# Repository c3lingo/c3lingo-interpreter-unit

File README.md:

# Conference Interpreter Unit
[c3lingo.org](https://c3lingo.org) is doing the great job of translating many talks of the Chaos Communication Congress and other CCC-related events to multiple languages.
But the required hardware for simultaneous translation is quite expensive to rent, even if it's "just" a specialized analog audio mixer.

So the idea was born to design an easy to use hardware with the special requirements of our interpreters in mind.

## Requirements
The hardware unit should deliver the native audio (stage/ hall mix) to the interpreter's headset and provide a sum of all interpreter's microphone to the input of the video streaming/ recording chain.
Mixing of the final translated audio (ducking the native audio with the translation) will be done as part of the streaming/ recording chain, so the interpreter unit should just provide the sum of all microphones.

Normally just 2 interpreters will provide one translation, but demanding talks might require 3 people.
So either 3 headphone inputs/ outputs should be provided or it must be possible to daisy-chain multiple units.

The user interface of the unit should be as simple, as possible to decrease the risk of mis-configuration.
This means, that no compressor and equalizer will be added in the input group.

General requirements:
- Line input of stage/ hall mix (native language) (XLR/ 6.3 mm balanced jack combo connector)
- 3x Microphone input (XLR) (at first just dynamic microphones)
    * VU-Meter for each input channel. (Perhaps with special color scheme: too quiet, good, too loud, clipping)
    * Fader/ Potentiometer for gain control
    * On-Air switch (on/ off position, with state LED)
    * Temporary mute button (momentary switch)
- 3x Headphone output (6.3 mm mono/ stereo (2x mono) jack)
    * Should output mix of native audio, own microphone and other translator's microphone
    * Potentiometer for output volume
    * Potentiometer for volume of own microphone in the mix
    * Potentiometer for volume of other two microphones in the mix
- Outputs:
    * Sum of all translators (XLR/ 6.3 mm balanced jack combo connector)

All inputs (besides the microphones) and outputs should:
- expect/ deliver a nominal level of +6dBu (~1.5 V RMS/ 4.3 V (p-p), german TV broadcast standard, 0 dBu = 0.775 V RMS)
- be transformer balanced and galvanically isolated

This results in a signal flow like this: 

## Status

### Tasks
- [x] Requirements collection
- [x] Electrical design draft/ proof of concept (breadboard)
- [x] Proof of concept validation
- [x] First PCB layout (prototyping modules)
- [x] More testing/ validation
- [x] Second PCB layout + casing prototype
    * [x] Channel strip schematic and PCB design
    * [x] Line I/O schematic and PCB design
    * [x] Power supply
- [x] More testing/ validation

Help is always appreciated!

### Implemented Requirements
- [x] Microphone input
- [x] Line input
- [x] Microphone summing and line output driver
- [x] Adjustable headphone mix and output volume
- [ ] ESD protection of line inputs and outputs
- [x] VU meter (own PCB)
- [x] VU meter (integrated in front panel PCB)
- [x] Mute and On-Air buttons

## Electrical Design
See [electrical-design.md](electrical-design.md).

Components marked as DNP (do not populate) are needed and need to be added.
The mark is just to generate the right BOM for ordering an assembled PBC with all SMD components, but no though-hole parts.

## User Interface
The user interface should enable the interpreters to adjust their microphone gain and headphone mix on their own.
Additionally, a (permanent) on/off switch, as well as a (temporary) mute button should be present.

A possible UI layout might look like this: 

See [hardware-selection.md](hardware-selection.md) for the selection of potentiometers and switches.

### Casing
The casing should be a desk console (angled surface), ideally with space at the front to mount the headset ports (XLR and 6.3 mm jack).
Since it can be quite difficult to drill holes and make the appropriate cutouts on the angled surface, we designed our own housing from bent sheet metal.
See the [mechanical/](mechanical/README.md) directory for additional information.

PCBs are split up by channel and mounting surface, so that dimensional tolerancen between the surfaces are not that critical.
The top plate should have a maximum thickness of 1.5 mm, the front and back can be slightly thicker at 2 mm.
All LEDs need to be mounted with some space to the PCB surface so that they can cover the 9 mm gap to the front plate and still stick through.
A mounting guide can be found at [mechanical/assembly-helpers](mechanical/assembly-helpers/vumeter-leds.scad).

## Notes
A dynamic microphone needs at least 50-60 dB gain in the pre-amp, because a typical signal is at about 1 - 100 uV (-118 to -78 dBu or -120 to -80 dBV).

Line level in professional audio gear is at +4 dBu, which is 1.228 V (RMS).
Because 0 dBu is defined as 1 mW at a load of 600 Ohm, which needs a voltage of 0.77 V.
Increasing the voltage by a factor of 10 is an amplification of 20 dB.

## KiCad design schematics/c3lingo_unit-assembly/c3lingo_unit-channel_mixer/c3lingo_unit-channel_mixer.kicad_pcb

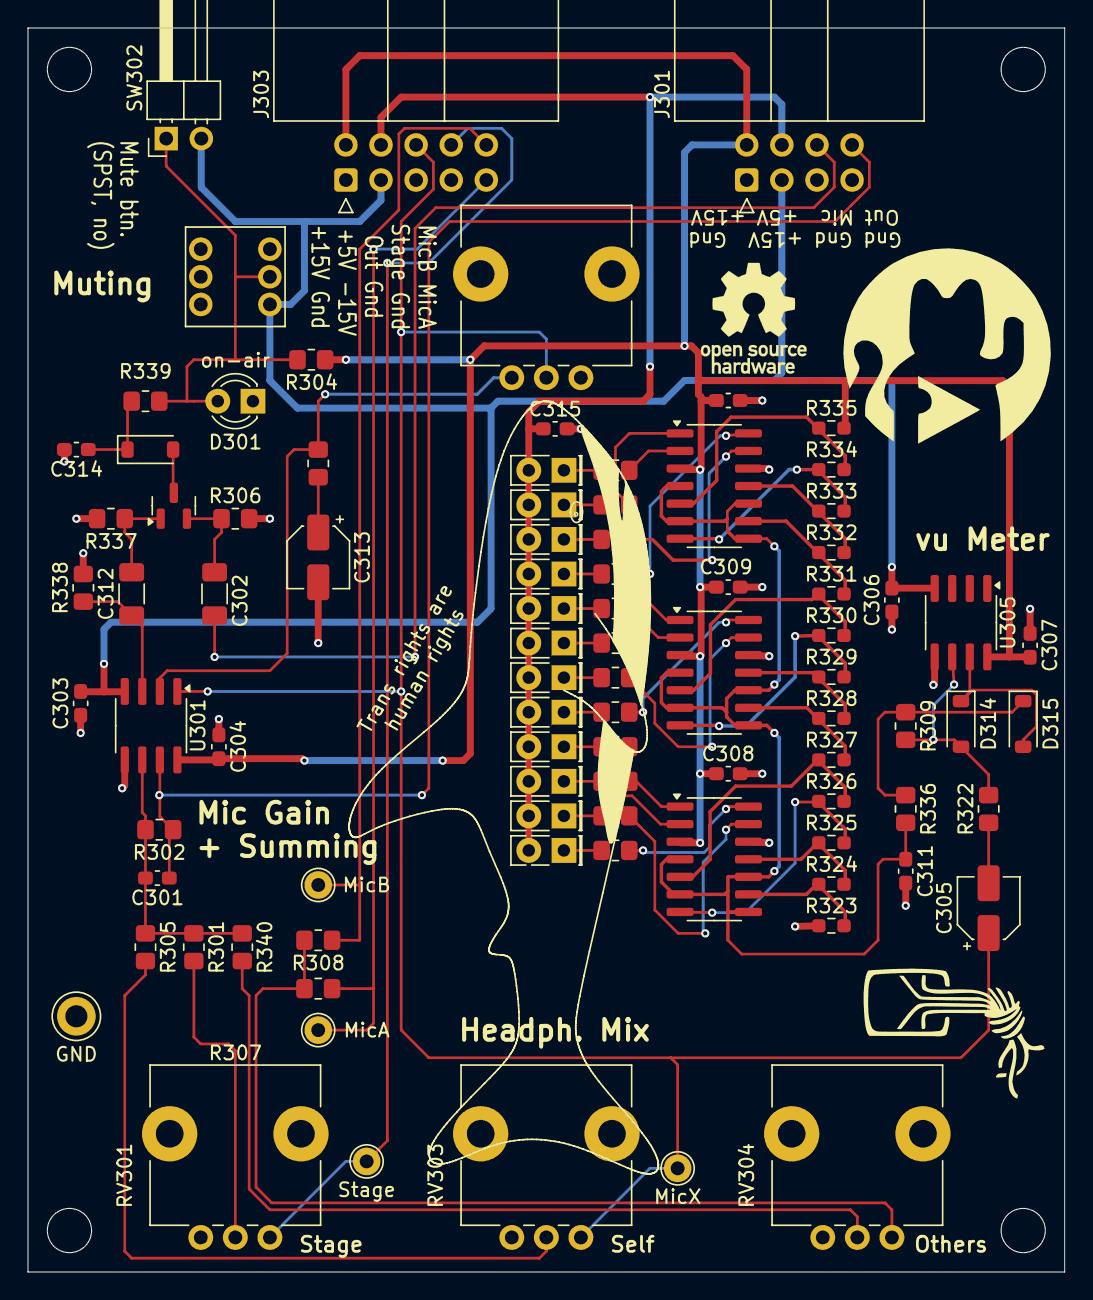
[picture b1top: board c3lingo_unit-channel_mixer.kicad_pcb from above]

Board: 2 copper layers, 75.0 x 90.0 mm, 94 parts (0 on the bottom side), 64 nets.

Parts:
C301: 680pF; C_0603_1608Metric_Pad1.08x0.95mm_HandSolder
C302, C312: 100nF C0G; C_1206_3216Metric_Pad1.33x1.80mm_HandSolder
C303, C304, C306, C307, C308, C309, C310, C311, C314, C315: 100nF; C_0603_1608Metric_Pad1.08x0.95mm_HandSolder
C305, C313: 1uF; CP_Elec_4x5.8
D301: on-air; LED_D3.0mm
D302, D303, D304, D305, D306, D307: ye; LED_Rectangular_W5.0mm_H2.0mm
D308, D309, D310: gn; LED_Rectangular_W5.0mm_H2.0mm
D311, D312, D313: rd; LED_Rectangular_W5.0mm_H2.0mm
D314, D315, D316: 1N4148; D_SOD-123
H301, H302, H303, H304: MountingHole; MountingHole_3.2mm_M3
J301: Interconnect; IDC-Header_2x04_P2.54mm_Horizontal
J303: I/O; IDC-Header_2x05_P2.54mm_Horizontal
Q301: MMBFJ113; SOT-23
R301, R302, R305: 22K; R_0805_2012Metric_Pad1.20x1.40mm_HandSolder
R303: 1.5K; R_0805_2012Metric_Pad1.20x1.40mm_HandSolder
R304: 3.3K; R_0805_2012Metric_Pad1.20x1.40mm_HandSolder
R306, R337, R338, R339: 1M; R_0805_2012Metric_Pad1.20x1.40mm_HandSolder
R307, R308: 2.2K; R_0805_2012Metric_Pad1.20x1.40mm_HandSolder
R309: 12K; R_0805_2012Metric_Pad1.20x1.40mm_HandSolder
R310, R311, R312, R313, R314, R315, R316, R317, R318, R319, R320, R321: 150R; R_0805_2012Metric_Pad1.20x1.40mm_HandSolder
R322: 1K; R_0805_2012Metric_Pad1.20x1.40mm_HandSolder
R323: 220R; R_0603_1608Metric_Pad0.98x0.95mm_HandSolder
R324: 100R; R_0603_1608Metric_Pad0.98x0.95mm_HandSolder
R325: 150R; R_0603_1608Metric_Pad0.98x0.95mm_HandSolder
R326: 180R; R_0603_1608Metric_Pad0.98x0.95mm_HandSolder
R327: 270R; R_0603_1608Metric_Pad0.98x0.95mm_HandSolder
R328: 390R; R_0603_1608Metric_Pad0.98x0.95mm_HandSolder
R329: 470R; R_0603_1608Metric_Pad0.98x0.95mm_HandSolder
R330: 680R; R_0603_1608Metric_Pad0.98x0.95mm_HandSolder
R331: 1.2K; R_0603_1608Metric_Pad0.98x0.95mm_HandSolder
R332: 1.5K; R_0603_1608Metric_Pad0.98x0.95mm_HandSolder
R333: 2.2K; R_0603_1608Metric_Pad0.98x0.95mm_HandSolder
R334: 3.3K; R_0603_1608Metric_Pad0.98x0.95mm_HandSolder
R335: 15K; R_0603_1608Metric_Pad0.98x0.95mm_HandSolder
R336: 100K; R_0805_2012Metric_Pad1.20x1.40mm_HandSolder
R340: 10K; R_0805_2012Metric_Pad1.20x1.40mm_HandSolder
RV301, RV302, RV303, RV304: 50K log.; Potentiometer_CUI_PTN09X_Single_Vertical
SW301: OnAir_X; SW_APEM_MHPS2273_DPDT
SW302: Mute_X; PinHeader_1x02_P2.54mm_Horizontal
TP301: Stage; TestPoint_THTPad_D2.0mm_Drill1.0mm
TP302: MicX; TestPoint_THTPad_D2.0mm_Drill1.0mm
TP303: MicA; TestPoint_THTPad_D2.0mm_Drill1.0mm
TP304: MicB; TestPoint_THTPad_D2.0mm_Drill1.0mm
TP305: GND; TestPoint_Keystone_5005-5009_Compact
U301: TL072; SOIC-8_3.9x4.9mm_P1.27mm
U302, U303, U304: LM339; SOIC-14_3.9x8.7mm_P1.27mm
U305: LM833-N; SOIC-8_3.9x4.9mm_P1.27mm

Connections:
+5V: C315.1, D302.2 (A), D303.2 (A), D304.2 (A), D305.2 (A), D306.2 (A), D307.2 (A), D308.2 (A), D309.2 (A), D310.2 (A), D311.2 (A), D312.2 (A), D313.2 (A), J301.4, J303.4
+15V: C304.2, C307.2, C308.1, C309.1, C310.1, J301.2, J303.2, R304.1, R335.2, U301.8 (V+), U302.3 (V+), U303.3 (V+), U304.3 (V+), U305.8 (V+)
-15V: C303.2, C306.2, J301.3, J303.3, SW301.3 (C), SW302.2, U301.4 (V-), U305.4 (V-)
/Headphone: C301.1, J301.8, R302.1, U301.7
/MicPre: C302.2, J301.6
/Mic_OthersA: J303.9, R307.1, TP303.1
/Mic_OthersB: J303.10, R308.1, TP304.1
/Mic_X: C305.1, J303.6, RV302.2, RV303.3, TP302.1, U301.1
/Stage: J303.8, RV301.3, TP301.1
GND: C303.1, C304.1, C306.1, C307.1, C308.2, C309.2, C310.2, C311.2, C313.2, C314.2, C315.2, D301.1 (K), J301.1, J301.5, J301.7, J303.1, J303.5, J303.7, R306.2, R323.1, R337.2, R338.2, RV301.1, RV303.1, RV304.1, TP305.1, U301.5 (+), U302.12 (V-), U303.12 (V-), U304.12 (V-), U305.5 (+)
unnamed: C305.2, R322.1
unnamed: C313.1, R303.2
unnamed: D301.2 (A), R304.2, R339.2, SW301.2 (B), SW302.1
unnamed: D302.1 (K), R310.1
unnamed: D303.1 (K), R311.1
unnamed: D304.1 (K), R312.1
unnamed: D305.1 (K), R313.1
unnamed: D306.1 (K), R314.1
unnamed: D307.1 (K), R315.1
unnamed: D308.1 (K), R316.1
unnamed: D309.1 (K), R317.1
unnamed: D310.1 (K), R318.1
unnamed: D311.1 (K), R319.1
unnamed: D312.1 (K), R320.1
unnamed: D313.1 (K), R321.1
unnamed: D314.2 (A), R309.2, R322.2, U305.6 (-)
unnamed: D314.1 (K), D315.2 (A), U305.7
unnamed: D315.1 (K), R309.1, R336.1
unnamed: D316.2 (A), Q301.3 (G)
unnamed: C314.1, D316.1 (K), R339.1
unnamed: C312.2, Q301.1 (D), R337.1
unnamed: C302.1, Q301.2 (S), R306.1
unnamed: R301.2, RV301.2
unnamed: R305.2, RV303.2
unnamed: R307.2, R308.2, RV304.3
unnamed: R310.2, U302.14
unnamed: R311.2, U302.13
unnamed: R312.2, U302.1
unnamed: R313.2, U302.2
unnamed: R314.2, U303.14
unnamed: R315.2, U303.13
unnamed: R316.2, U303.1
unnamed: R317.2, U303.2
unnamed: R318.2, U304.14
unnamed: R319.2, U304.13
unnamed: R320.2, U304.1
unnamed: R321.2, U304.2
unnamed: R340.2, RV304.2
unnamed: C312.1, R338.1, U301.3 (+)
unnamed: R303.1, RV302.1, U301.2 (-)
unnamed: C301.2, R301.1, R302.2, R305.1, R340.1, U301.6 (-)
unnamed: R326.2, R327.1, U302.5 (+)
unnamed: C311.1, R336.2, U302.4 (-), U302.6 (-), U302.8 (-), U302.10 (-), U303.4 (-), U303.6 (-), U303.8 (-), U303.10 (-), U304.4 (-), U304.6 (-), U304.8 (-), U304.10 (-)
unnamed: R325.2, R326.1, U302.7 (+)
unnamed: R324.2, R325.1, U302.11 (+)
unnamed: R323.2, R324.1, U302.9 (+)
unnamed: R330.2, R331.1, U303.5 (+)
unnamed: R329.2, R330.1, U303.7 (+)
unnamed: R328.2, R329.1, U303.11 (+)
unnamed: R327.2, R328.1, U303.9 (+)
unnamed: R334.2, R335.1, U304.5 (+)
unnamed: R333.2, R334.1, U304.7 (+)
unnamed: R332.2, R333.1, U304.11 (+)
unnamed: R331.2, R332.1, U304.9 (+)

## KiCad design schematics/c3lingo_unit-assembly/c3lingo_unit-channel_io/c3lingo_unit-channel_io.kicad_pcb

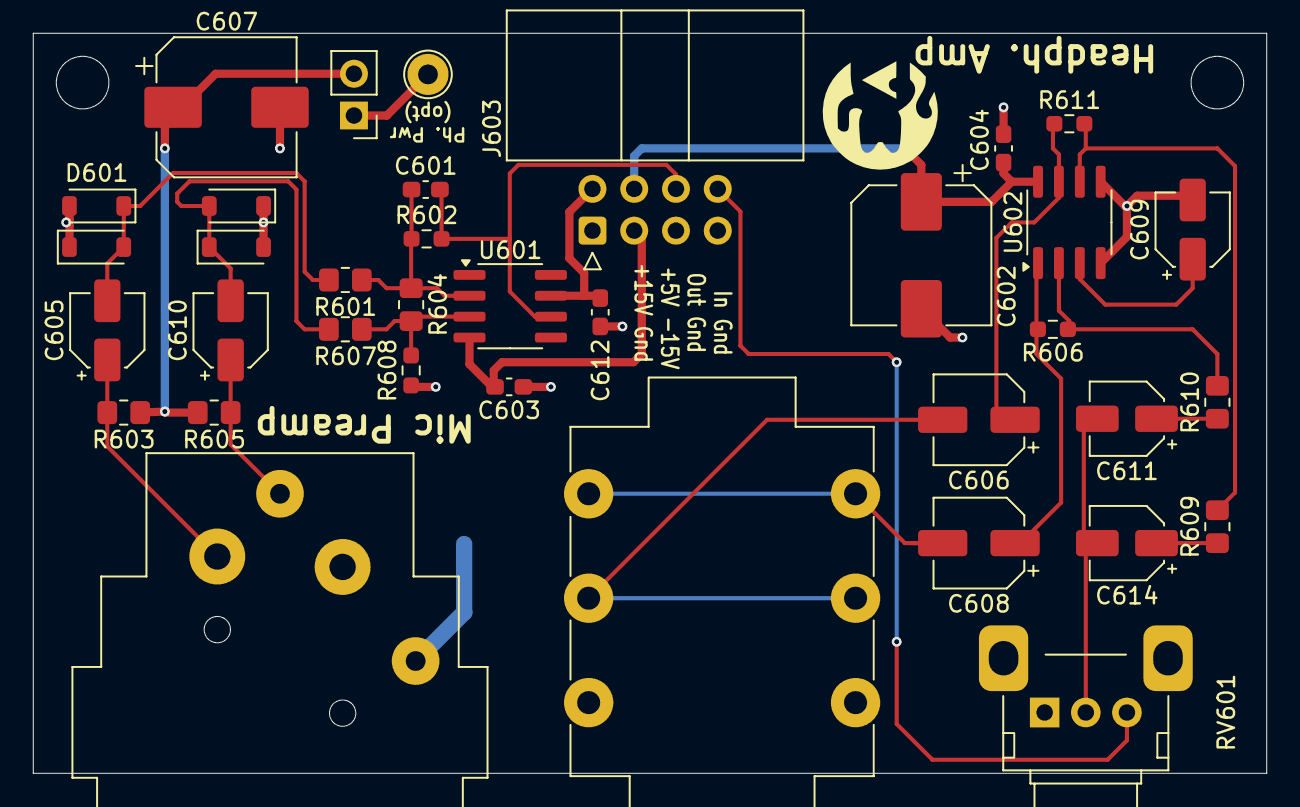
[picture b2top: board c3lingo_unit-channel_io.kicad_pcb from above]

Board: 2 copper layers, 75.0 x 45.0 mm, 39 parts (1 on the bottom side), 25 nets.

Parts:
C601: 330p; C_0603_1608Metric_Pad1.08x0.95mm_HandSolder
C602: 100uF; CP_Elec_8x10
C603, C604, C612: 100nF, lowESR; C_0603_1608Metric_Pad1.08x0.95mm_HandSolder
C605, C610: 1uF/ 63V lowESR; CP_Elec_4x5.8
C606, C608: 68uF lowESR; CP_Elec_5x5.8
C607: 100uF/ 50V; CP_Elec_8x10
C609: 1uF lowESR; CP_Elec_4x5.8
C611, C614: 1uF; CP_Elec_4x5.8
D601, D602, D603, D604: 1N4148; D_SOD-123
H601, H602: MountingHole; MountingHole_3.2mm_M3
J601: Mic X In; Jack_XLR_Neutrik_NC3FAAH2_Horizontal
J602: Headphone X; Jack_6.35mm_Neutrik_NMJ6HFD2_Horizontal
J603: Interconnect; IDC-Header_2x04_P2.54mm_Horizontal
JP601: GND_JMP; SolderJumper-2_P1.3mm_Open_TrianglePad1.0x1.5mm
JP602: Phant. Pwr; PinHeader_1x02_P2.54mm_Vertical
R601, R607: 1K 1%; R_0805_2012Metric_Pad1.20x1.40mm_HandSolder
R602, R608: 39K 1%; R_0603_1608Metric_Pad0.98x0.95mm_HandSolder
R603, R605: 6.8K 1%; R_0805_2012Metric_Pad1.20x1.40mm_HandSolder
R604: 27K 1%; R_0805_2012Metric_Pad1.20x1.40mm_HandSolder
R606, R611: 39K; R_0603_1608Metric_Pad0.98x0.95mm_HandSolder
R609, R610: 10K; R_0805_2012Metric_Pad1.20x1.40mm_HandSolder
RV601: 50K log.; Potentiometer_Alps_RK09K_Single_Horizontal
TP601: Phantom Power; TestPoint_THTPad_D2.5mm_Drill1.2mm
U601: NE5534; SOIC-8_3.9x4.9mm_P1.27mm
U602: TPA6111A2; SOIC-8_3.9x4.9mm_P1.27mm

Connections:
+5V: C602.1, C604.1, J603.4, U602.8 (VDD)
+15V: C612.1, J603.2, U601.7 (V+)
-15V: C603.2, J603.3, U601.4 (V-)
/Headphone: J603.8, RV601.3
/MicPre: C601.2, J603.6, R602.2, U601.6
GND: C602.2, C603.1, C604.2, C607.2, C609.2, C612.2, D601.2 (A), D602.1 (K), D603.1 (K), D604.2 (A), J601.1, J602.S, J602.SN, J603.1, J603.5, J603.7, JP601.1 (A), R608.1, RV601.1, U602.4 (GND), U602.5 (SHDN)
GNDREF: J601.G, JP601.2 (B)
unnamed: C605.1, J601.2, R603.2
unnamed: C606.2, J602.R, J602.RN
unnamed: C608.2, J602.T, J602.TN
unnamed: C610.1, J601.3, R605.1
unnamed: C611.1, R610.1
unnamed: C611.2, C614.2, RV601.2
unnamed: C614.1, R609.1
unnamed: C605.2, D601.1 (K), D602.2 (A), R601.2
unnamed: C610.2, D603.2 (A), D604.1 (K), R607.2
unnamed: JP602.1 (A), TP601.1
unnamed: R604.2, R607.1, R608.2, U601.3 (+)
unnamed: C601.1, R601.1, R602.1, R604.1, U601.2 (-)
unnamed: C609.1, U602.3 (BYPASS)
unnamed: R606.1, R610.2, U602.2 (IN1-)
unnamed: R609.2, R611.2, U602.6 (IN2-)
unnamed: C608.1, R606.2, U602.1 (VO1)
unnamed: C606.1, R611.1, U602.7 (VO2)
V_Phant: C607.1, JP602.2 (B), R603.1, R605.2

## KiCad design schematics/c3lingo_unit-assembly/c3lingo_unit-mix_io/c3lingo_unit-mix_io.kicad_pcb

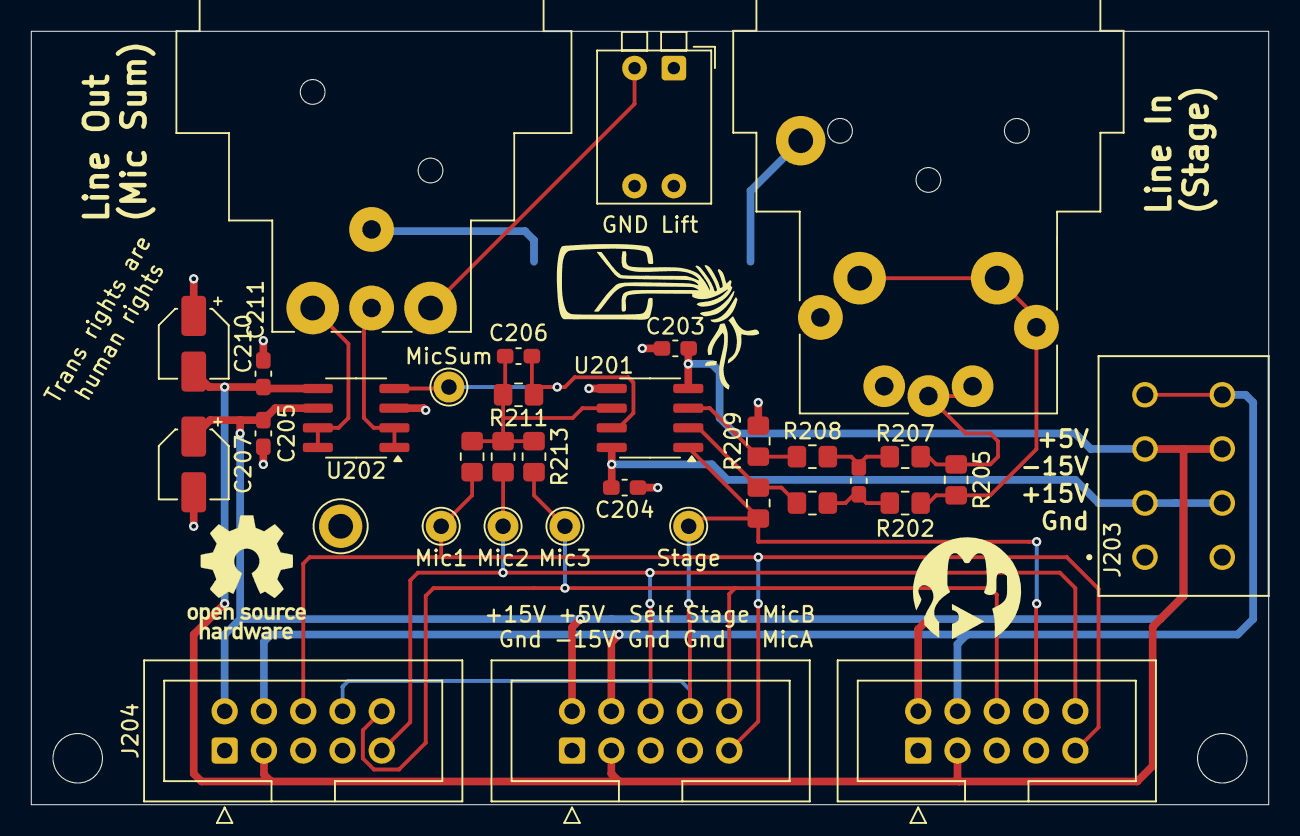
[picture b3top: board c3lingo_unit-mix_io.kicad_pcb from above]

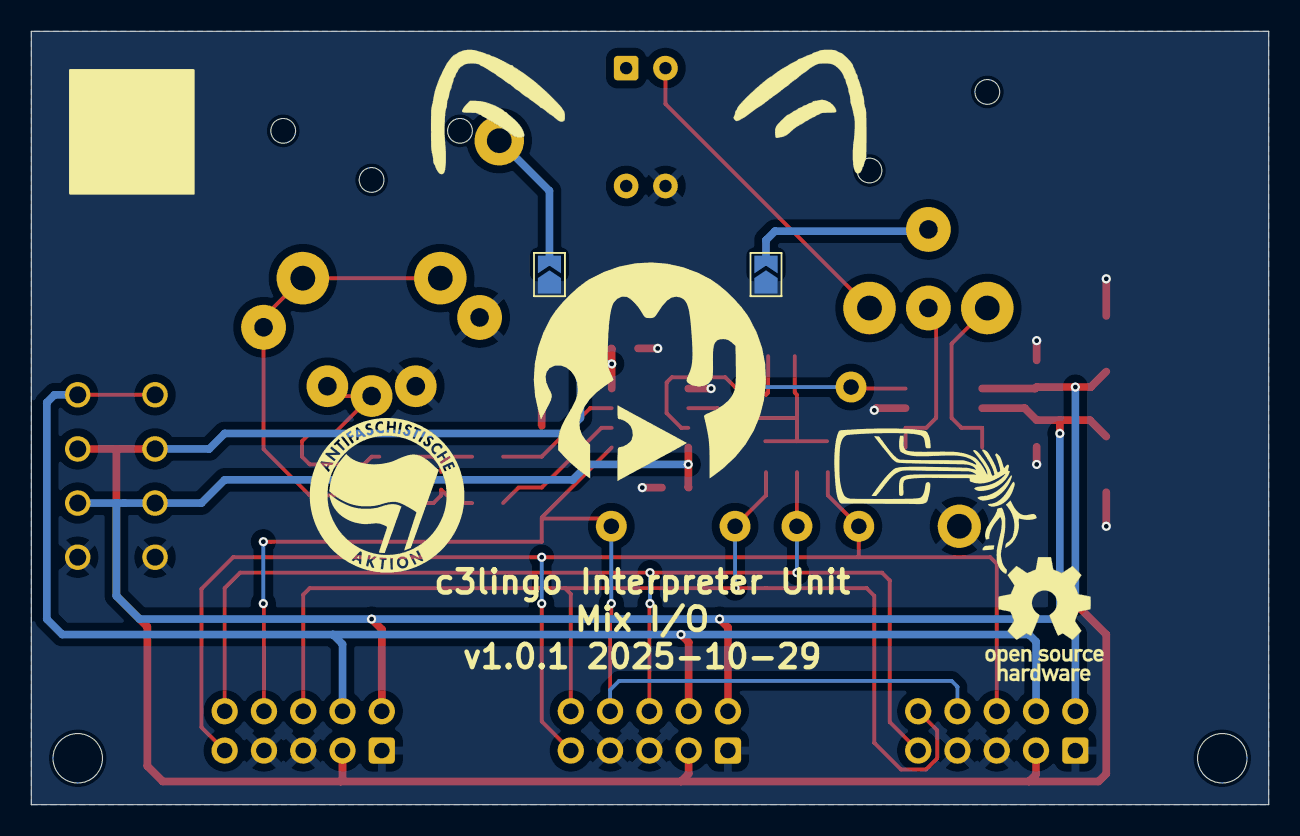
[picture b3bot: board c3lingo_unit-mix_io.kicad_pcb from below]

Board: 2 copper layers, 80.0 x 50.0 mm, 38 parts (2 on the bottom side), 20 nets.

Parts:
C202: 220pF; C_0603_1608Metric_Pad1.08x0.95mm_HandSolder
C203, C204, C205, C211: 100nF; C_0603_1608Metric_Pad1.08x0.95mm_HandSolder
C206: 22pF; C_0603_1608Metric_Pad1.08x0.95mm_HandSolder
C207, C210: 10uF; CP_Elec_4x5.4
H201, H202: MountingHole; MountingHole_3.2mm_M3
J201: Stage Line-In; Jack_XLR-6.35mm_Neutrik_NCJ6FA-H_Horizontal
J202: Mix Line-Out; Jack_XLR_Neutrik_NC3MAAH_Horizontal
J203: PowerSupply; TerminalBlock_Phoenix_SPTAF-1-4-3.5_1x04_P3.5mm
J204: Ch1; IDC-Header_2x05_P2.54mm_Vertical
J205: Ch2; IDC-Header_2x05_P2.54mm_Vertical
J206: Ch3; IDC-Header_2x05_P2.54mm_Vertical
JP201, JP202: GND_JMP; SolderJumper-2_P1.3mm_Open_TrianglePad1.0x1.5mm
R201, R202, R203, R207, R208, R209, R211: 10K; R_0805_2012Metric_Pad1.20x1.40mm_HandSolder
R205: 3.3K; R_0805_2012Metric_Pad1.20x1.40mm_HandSolder
R210, R212, R213: 22K; R_0805_2012Metric_Pad1.20x1.40mm_HandSolder
SW201: GND Lift; SW_DIP_SPSTx02_Piano_CTS_Series194-2MSTN_W7.62mm_P2.54mm
TP201: Stage; TestPoint_THTPad_D2.0mm_Drill1.0mm
TP202: Mic1; TestPoint_THTPad_D2.0mm_Drill1.0mm
TP203: Mic2; TestPoint_THTPad_D2.0mm_Drill1.0mm
TP204: MicSum; TestPoint_THTPad_D2.0mm_Drill1.0mm
TP205: Mic3; TestPoint_THTPad_D2.0mm_Drill1.0mm
TP206: GND; TestPoint_Keystone_5005-5009_Compact
U201: LM833-N; SOIC-8_3.9x4.9mm_P1.27mm
U202: DRV135UA; SOIC-8_3.9x4.9mm_P1.27mm

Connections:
+5V: J203.4, J204.4, J205.4, J206.4
+15V: C204.2, C205.1, C207.1, J203.2, J204.2, J205.2, J206.2, U201.8 (V+), U202.6 (V+)
-15V: C203.2, C210.2, C211.1, J203.3, J204.3, J205.3, J206.3, U201.4 (V-), U202.5 (V-)
/Mic_Ch1: J204.6, J205.9, J206.9, R210.2, TP202.1
/Mic_Ch2: J204.9, J205.6, J206.10, R212.2, TP203.1
/Mic_Ch3: J204.10, J205.10, J206.6, R213.2, TP205.1
/Stage: J204.8, J205.8, J206.8, R201.1, TP201.1, U201.1
GND: C203.1, C204.1, C205.2, C207.2, C210.1, C211.2, J201.1, J201.S, J203.1, J204.1, J204.5, J204.7, J205.1, J205.5, J205.7, J206.1, J206.5, J206.7, JP201.1 (A), JP202.1 (A), R209.2, SW201.3, TP206.1, U201.5 (+), U202.3 (GND)
GNDREF: J201.G, J202.G, JP201.2 (B), JP202.2 (B)
unnamed: C202.1, R202.2, R203.2
unnamed: C202.2, R207.2, R208.2
unnamed: J201.2, J201.T, R202.1, R205.2
unnamed: J201.3, J201.R, R205.1, R207.1
unnamed: J202.1, SW201.2
unnamed: R208.1, R209.1, U201.3 (+)
unnamed: R201.2, R203.1, U201.2 (-)
unnamed: C206.2, R210.1, R211.2, R212.1, R213.1, U201.6 (-)
unnamed: J202.2, U202.7 (SENSE+), U202.8 (VO+)
unnamed: J202.3, U202.1 (VO-), U202.2 (SENSE-)
unnamed: C206.1, R211.1, TP204.1, U201.7, U202.4 (VIN)

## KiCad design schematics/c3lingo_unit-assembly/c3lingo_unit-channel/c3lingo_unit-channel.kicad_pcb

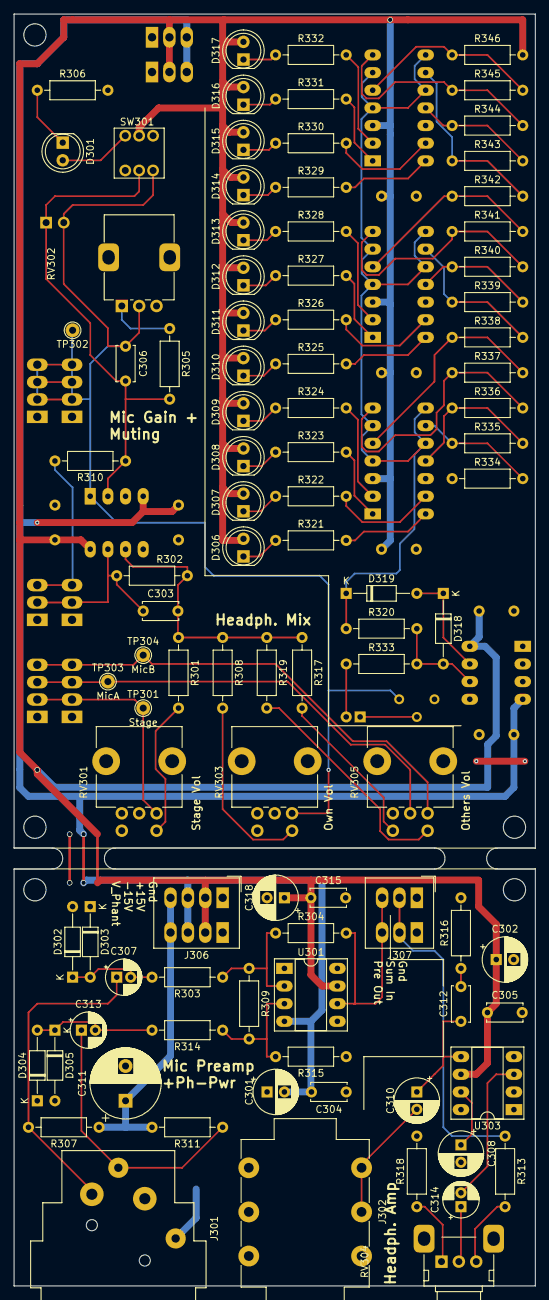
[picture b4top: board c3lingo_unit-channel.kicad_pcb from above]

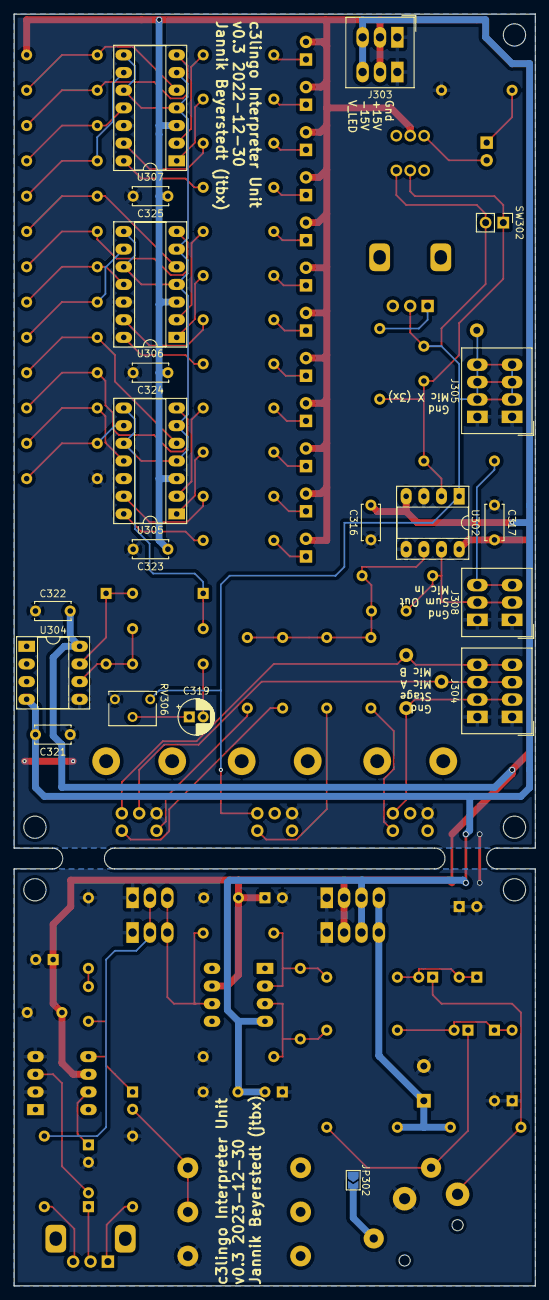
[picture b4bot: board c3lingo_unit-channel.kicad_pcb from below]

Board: 2 copper layers, 75.0 x 183.0 mm, 120 parts (20 on the bottom side), 77 nets.

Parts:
C301, C302, C308, C318: 100uF; CP_Radial_D6.3mm_P2.50mm
C303: 22pF; C_Disc_D5.0mm_W2.5mm_P5.00mm
C304, C305, C306, C315, C316, C317, C321, C322, C323, C324, C325: 100nF; C_Disc_D5.0mm_W2.5mm_P5.00mm
C307, C313: 1uF/ 63V lowESR; CP_Radial_D5.0mm_P2.00mm
C310: 220uF lowESR; CP_Radial_D6.3mm_P2.50mm
C311: 100uF/ 63V; CP_Radial_D10.0mm_P5.00mm
C312: 47nF; C_Disc_D5.0mm_W2.5mm_P5.00mm
C314, C319: 1uF; CP_Radial_D5.0mm_P2.00mm
D301: On-Air (rd); LED_D5.0mm
D302, D303, D304, D305, D318, D319: 1N4148; D_DO-35_SOD27_P10.16mm_Horizontal
D306, D307, D308, D309, D317: rd; LED_D5.0mm
D310, D311, D315, D316: ye; LED_D5.0mm
D312, D313, D314: gn; LED_D5.0mm
H301, H302, H303, H305, H306: MountingHole; MountingHole_3.2mm_M3
J301: Mic X In; Jack_XLR_Neutrik_NC3FAAH2_Horizontal
J302: Headphone X; Jack_6.35mm_Neutrik_NMJ6HFD2_Horizontal
J303: PowerSupply; TerminalBlock_Phoenix_PTSM-0,5-3-2.5-H-THR_1x03_P2.50mm_Hor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
J304: Inputs; TerminalBlock_Phoenix_PTSM-0,5-4-2.5-H-THR_1x04_P2.50mm_Hor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
J305: Output; TerminalBlock_Phoenix_PTSM-0,5-4-2.5-H-THR_1x04_P2.50mm_Hor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
J306: PowerSupply; TerminalBlock_Phoenix_PTSM-0,5-4-2.5-H-THR_1x04_P2.50mm_Hor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
J307, J308: Interconnect; TerminalBlock_Phoenix_PTSM-0,5-3-2.5-H-THR_1x03_P2.50mm_Hor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
JP302: GND_JMP; SolderJumper-2_P1.3mm_Open_TrianglePad1.0x1.5mm
R301, R302, R308, R317, R319: 22K; R_Axial_DIN0207_L6.3mm_D2.5mm_P10.16mm_Horizontal
R303, R314: 1K 1%; R_Axial_DIN0207_L6.3mm_D2.5mm_P10.16mm_Horizontal
R304, R315: 330K 1%; R_Axial_DIN0207_L6.3mm_D2.5mm_P10.16mm_Horizontal
R305: 56R; R_Axial_DIN0207_L6.3mm_D2.5mm_P10.16mm_Horizontal
R306, R341: 680R; R_Axial_DIN0207_L6.3mm_D2.5mm_P10.16mm_Horizontal
R307, R311: 6.8K 1%; R_Axial_DIN0207_L6.3mm_D2.5mm_P10.16mm_Horizontal
R309: 27K 1%; R_Axial_DIN0207_L6.3mm_D2.5mm_P10.16mm_Horizontal
R310: 330R; R_Axial_DIN0207_L6.3mm_D2.5mm_P10.16mm_Horizontal
R313: 330K; R_Axial_DIN0207_L6.3mm_D2.5mm_P10.16mm_Horizontal
R316: 12R; R_Axial_DIN0207_L6.3mm_D2.5mm_P10.16mm_Horizontal
R318: 2.2K; R_Axial_DIN0207_L6.3mm_D2.5mm_P10.16mm_Horizontal
R320: 15K; R_Axial_DIN0207_L6.3mm_D2.5mm_P10.16mm_Horizontal
R321, R322, R323, R324, R325, R326, R327, R328, R329, R330, R331, R332, R340: 390R; R_Axial_DIN0207_L6.3mm_D2.5mm_P10.16mm_Horizontal
R333, R342: 1K; R_Axial_DIN0207_L6.3mm_D2.5mm_P10.16mm_Horizontal
R334, R336: 68R; R_Axial_DIN0207_L6.3mm_D2.5mm_P10.16mm_Horizontal
R335: 39R; R_Axial_DIN0207_L6.3mm_D2.5mm_P10.16mm_Horizontal
R337: 100R; R_Axial_DIN0207_L6.3mm_D2.5mm_P10.16mm_Horizontal
R338: 150R; R_Axial_DIN0207_L6.3mm_D2.5mm_P10.16mm_Horizontal
R339: 270R; R_Axial_DIN0207_L6.3mm_D2.5mm_P10.16mm_Horizontal
R343: 1.5K; R_Axial_DIN0207_L6.3mm_D2.5mm_P10.16mm_Horizontal
R344, R346: 2.7K; R_Axial_DIN0207_L6.3mm_D2.5mm_P10.16mm_Horizontal
R345: 3.9K; R_Axial_DIN0207_L6.3mm_D2.5mm_P10.16mm_Horizontal
RV301, RV303: 50K log.; Potentiometer_Alps_RK09K_Double_Vertical
RV302: 10K log.; Potentiometer_Alps_RK09K_Single_Vertical
RV304: 50K log.; Potentiometer_Alps_RK09K_Single_Horizontal
RV305: 50K log. st.; Potentiometer_Alps_RK09K_Double_Vertical
RV306: 50K; Potentiometer_Vishay_T73XX_Horizontal
SW301: OnAir_X; SW_APEM_MHPS2273_DPDT
SW302: Mute_X; PinHeader_1x02_P2.54mm_Vertical
TP301: Stage; TestPoint_THTPad_D2.0mm_Drill1.0mm
TP302: MicX; TestPoint_THTPad_D2.0mm_Drill1.0mm
TP303: MicA; TestPoint_THTPad_D2.0mm_Drill1.0mm
TP304: MicB; TestPoint_THTPad_D2.0mm_Drill1.0mm
U301: NE5534; DIP-8_W7.62mm_Socket_LongPads
U302, U304: LM833N; DIP-8_W7.62mm_Socket_LongPads
U303: LM386N-4; DIP-8_W7.62mm_Socket_LongPads
U305, U306, U307: LM339; DIP-14_W7.62mm_Socket_LongPads

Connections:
+15V: C302.1, C305.1, C315.1, C317.2, C318.1, C322.2, C323.1, C324.1, C325.1, D306.2 (A), D307.2 (A), D308.2 (A), D309.2 (A), D310.2 (A), D311.2 (A), D312.2 (A), D313.2 (A), D314.2 (A), D315.2 (A), D316.2 (A), D317.2 (A), J303.2, J306.2, R346.2, SW301.5 (B), U301.7 (V+), U302.8 (V+), U303.6 (V+), U304.8 (V+), U305.3 (V+), U306.3 (V+), U307.3 (V+)
-15V: C301.2, C304.2, C316.2, C321.2, J303.3, J306.3, U301.4 (V-), U302.4 (V-), U304.4 (V-)
/Monitor_OthersA: J304.3, RV305.6, TP303.1
/Monitor_OthersB: J304.4, RV305.3, TP304.1
/Monitor_Stage: J304.2, RV301.3, TP301.1
/PreampOut: C306.1, J305.2, J305.3, J305.4, RV302.2, RV303.3, RV306.1, SW301.1 (A), SW302.2, TP302.1, U302.1
AmpIn: J307.2, R313.1
GND: C301.1, C302.2, C304.1, C305.2, C308.2, C311.2, C315.2, C316.1, C317.1, C318.2, C321.1, C322.1, C323.2, C324.2, C325.2, D302.2 (A), D303.1 (K), D304.1 (K), D305.2 (A), J301.1, J302.S, J303.1, J304.1, J305.1, J306.1, J307.1, J308.1, JP302.1 (A), R306.2, R315.1, R316.2, R318.2, R334.1, RV301.1, RV303.1, RV305.1, RV306.3, U302.3 (+), U302.5 (+), U303.2 (-), U303.4 (GND), U304.5 (+), U305.12 (V-), U306.12 (V-), U307.12 (V-)
GNDREF: J301.G, JP302.2 (B)
MicGainIn: J308.3, R310.2
MicPreOut: J307.3, R304.2, U301.6
unnamed: C303.2, R301.1, R302.2, R308.1, R317.1, R319.1, U302.6 (-)
unnamed: C306.2, R305.2, R310.1, SW301.2 (B), SW302.1, U302.2 (-)
unnamed: C307.1, J301.2, R307.2
unnamed: C307.2, D302.1 (K), D303.2 (A), R303.2
unnamed: C308.1, U303.7 (BYPASS)
unnamed: C310.1, C312.1, U303.5
unnamed: C310.2, J302.R, J302.T
unnamed: C312.2, R316.1
unnamed: C313.1, J301.3, R311.1
unnamed: C313.2, D304.2 (A), D305.1 (K), R314.2
unnamed: C314.1, RV304.2
unnamed: C314.2, U303.3 (+)
unnamed: C319.1, RV306.2
unnamed: C319.2, R333.1
unnamed: D301.1 (K), R306.1
unnamed: D301.2 (A), SW301.6 (C)
unnamed: D306.1 (K), R321.1
unnamed: D307.1 (K), R322.1
unnamed: D308.1 (K), R323.1
unnamed: D309.1 (K), R324.1
unnamed: D310.1 (K), R325.1
unnamed: D311.1 (K), R326.1
unnamed: D312.1 (K), R327.1
unnamed: D313.1 (K), R328.1
unnamed: D314.1 (K), R329.1
unnamed: D315.1 (K), R330.1
unnamed: D316.1 (K), R331.1
unnamed: D317.1 (K), R332.1
unnamed: D318.1 (K), D319.2 (A), U304.7
unnamed: D318.2 (A), R320.2, R333.2, U304.6 (-)
unnamed: D319.1 (K), R320.1, U305.4 (-), U305.6 (-), U305.8 (-), U305.10 (-), U306.4 (-), U306.6 (-), U306.8 (-), U306.10 (-), U307.4 (-), U307.6 (-), U307.8 (-), U307.10 (-)
unnamed: R301.2, RV301.2
unnamed: R303.1, R304.1, R309.1, U301.2 (-)
unnamed: R305.1, RV302.1
unnamed: R308.2, RV303.2
unnamed: R309.2, R314.1, R315.2, U301.3 (+)
unnamed: R313.2, RV304.3
unnamed: R317.2, RV305.5
unnamed: R318.1, RV304.1
unnamed: R319.2, RV305.2
unnamed: R321.2, U305.14
unnamed: R322.2, U305.13
unnamed: R323.2, U305.1
unnamed: R324.2, U305.2
unnamed: R325.2, U306.14
unnamed: R326.2, U306.13
unnamed: R327.2, U306.1
unnamed: R328.2, U306.2
unnamed: R329.2, U307.14
unnamed: R330.2, U307.13
unnamed: R331.2, U307.1
unnamed: R332.2, U307.2
unnamed: R334.2, R335.1, U305.9 (+)
unnamed: R335.2, R336.1, U305.11 (+)
unnamed: R336.2, R337.1, U305.7 (+)
unnamed: R337.2, R338.1, U305.5 (+)
unnamed: R338.2, R339.1, U306.9 (+)
unnamed: R339.2, R340.1, U306.11 (+)
unnamed: R340.2, R341.1, U306.7 (+)
unnamed: R341.2, R342.1, U306.5 (+)
unnamed: R342.2, R343.1, U307.9 (+)
unnamed: R343.2, R344.1, U307.11 (+)
unnamed: R344.2, R345.1, U307.7 (+)
unnamed: R345.2, R346.1, U307.5 (+)
SumOut: C303.1, J308.2, R302.1, U302.7
V_Phant: C311.1, J306.4, R307.1, R311.2

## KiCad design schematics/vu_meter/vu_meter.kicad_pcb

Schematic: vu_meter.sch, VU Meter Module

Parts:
C1, C2, C3, C4, C7: 100nF; C_Disc_D5.0mm_W2.5mm_P5.00mm
C5: 1uF; CP_Radial_D5.0mm_P2.50mm
C6: 47uF; CP_Radial_D10.0mm_P2.50mm_P5.00mm
D1: +12 rd; LED_D5.0mm
D2: +8 ye; LED_D5.0mm
D3: +4 ye; LED_D5.0mm
D4: 0 gn; LED_D5.0mm
D5: -4 gn; LED_D5.0mm
D6: -8 gn; LED_D5.0mm
D7: -12 ye; LED_D5.0mm
D8: -16 ye; LED_D5.0mm
D9: -20 rd; LED_D5.0mm
D10: -24 rd; LED_D5.0mm
D11: -28 rd; LED_D5.0mm
D12: -32 rd; LED_D5.0mm
D13, D14: 1N4148; D_DO-35_SOD27_P10.16mm_Horizontal
H1, H2, H3, H4: MountingHole; MountingHole_3.2mm_M3_ISO14580
J1: Pwr_Signal; PinHeader_1x04_P2.54mm_Vertical
R1, R2, R3, R4, R5, R6, R7, R8, R9, R10, R11, R12, R106: 390R; R_Axial_DIN0207_L6.3mm_D2.5mm_P10.16mm_Horizontal
R13, R104: 1K; R_Axial_DIN0207_L6.3mm_D2.5mm_P10.16mm_Horizontal
R14, R101: 3.9K; R_Axial_DIN0207_L6.3mm_D2.5mm_P10.16mm_Horizontal
R15: 100K; R_Axial_DIN0207_L6.3mm_D2.5mm_P10.16mm_Horizontal
R100, R102: 2.7K; R_Axial_DIN0207_L6.3mm_D2.5mm_P10.16mm_Horizontal
R103: 1.5K; R_Axial_DIN0207_L6.3mm_D2.5mm_P10.16mm_Horizontal
R105: 680R; R_Axial_DIN0207_L6.3mm_D2.5mm_P10.16mm_Horizontal
R107: 270R; R_Axial_DIN0207_L6.3mm_D2.5mm_P10.16mm_Horizontal
R108: 150R; R_Axial_DIN0207_L6.3mm_D2.5mm_P10.16mm_Horizontal
R109: 100R; R_Axial_DIN0207_L6.3mm_D2.5mm_P10.16mm_Horizontal
R110, R112: 68R; R_Axial_DIN0207_L6.3mm_D2.5mm_P10.16mm_Horizontal
R111: 39R; R_Axial_DIN0207_L6.3mm_D2.5mm_P10.16mm_Horizontal
RV1: 50K; Potentiometer_Vishay_T73XX_Horizontal
U1: LM833N; DIP-8_W7.62mm_Socket_LongPads
U2, U3, U4: LM339; DIP-14_W7.62mm_Socket_LongPads

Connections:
+15V: C1.2, C2.1, C3.1, C4.1, D1.2 (A), D2.2 (A), D3.2 (A), D4.2 (A), D5.2 (A), D6.2 (A), D7.2 (A), D8.2 (A), D9.2 (A), D10.2 (A), D11.2 (A), D12.2 (A), J1.3, R100.2, U1.8 (V+), U2.3 (V+), U3.3 (V+), U4.3 (V+)
-15V: C7.2, J1.2, U1.4 (V-)
Line_Input: J1.4, RV1.1
unnamed: C5.1, RV1.2
unnamed: C5.2, R13.1
unnamed: C6.1, D14.1 (K), R14.1, R15.1, U2.4 (-), U2.6 (-), U2.8 (-), U2.10 (-), U3.4 (-), U3.6 (-), U3.8 (-), U3.10 (-), U4.4 (-), U4.6 (-), U4.8 (-), U4.10 (-)
unnamed: D1.1 (K), R1.1
unnamed: D2.1 (K), R2.1
unnamed: D3.1 (K), R3.1
unnamed: D4.1 (K), R4.1
unnamed: D5.1 (K), R5.1
unnamed: D6.1 (K), R6.1
unnamed: D7.1 (K), R7.1
unnamed: D8.1 (K), R8.1
unnamed: D9.1 (K), R9.1
unnamed: D10.1 (K), R10.1
unnamed: D11.1 (K), R11.1
unnamed: D12.1 (K), R12.1
unnamed: D13.1 (K), D14.2 (A), U1.1
unnamed: D13.2 (A), R13.2, R14.2, U1.2 (-)
unnamed: R1.2, U2.2
unnamed: R2.2, U2.1
unnamed: R3.2, U2.13
unnamed: R4.2, U2.14
unnamed: R5.2, U3.2
unnamed: R6.2, U3.1
unnamed: R7.2, U3.13
unnamed: R8.2, U3.14
unnamed: R9.2, U4.2
unnamed: R10.2, U4.1
unnamed: R11.2, U4.13
unnamed: R12.2, U4.14
unnamed: R100.1, R101.2, U2.5 (+)
unnamed: R101.1, R102.2, U2.7 (+)
unnamed: R102.1, R103.2, U2.11 (+)
unnamed: R103.1, R104.2, U2.9 (+)
unnamed: R104.1, R105.2, U3.5 (+)
unnamed: R105.1, R106.2, U3.7 (+)
unnamed: R106.1, R107.2, U3.11 (+)
unnamed: R107.1, R108.2, U3.9 (+)
unnamed: R108.1, R109.2, U4.5 (+)
unnamed: R109.1, R110.2, U4.7 (+)
unnamed: R110.1, R111.2, U4.11 (+)
unnamed: R111.1, R112.2, U4.9 (+)

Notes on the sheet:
Buffer/ Rectifier Gain: 3.9
+12 dBu
+8 dBu
+0 dBu
+4 dBu
-32 dBu
-20 dBu
-8 dBu
-4 dBu
-12 dBu
-16 dBu
-24 dBu
-28 dBu
Signal Smoothing TODO: Remove all together!?
For Input Gain of 3.9: 2700 Ω: 11,99 dBu 3900 Ω: 8,12 dBu 2700 Ω: 3,86 dBu 1500 Ω: 0,1 dBu 1000 Ω: -3,8 dBu 680 Ω: -8,03 dBu 390 Ω: -11,89 dBu 270 Ω: -16,17 dBu 150 Ω: -19,95 dBu 100 Ω: -23,87 dBu 68 Ω: -28,15 dBu 39 Ω: -32,08 dBu 68 Ω to ground 1.11 mA @ 15V (13.565 kΩ)
TODO: Better use 5V? rd: 2.3 V (390R @15V) gn: 2.4 V (390R @15V) ye: 2.6 V (390R @15V)

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
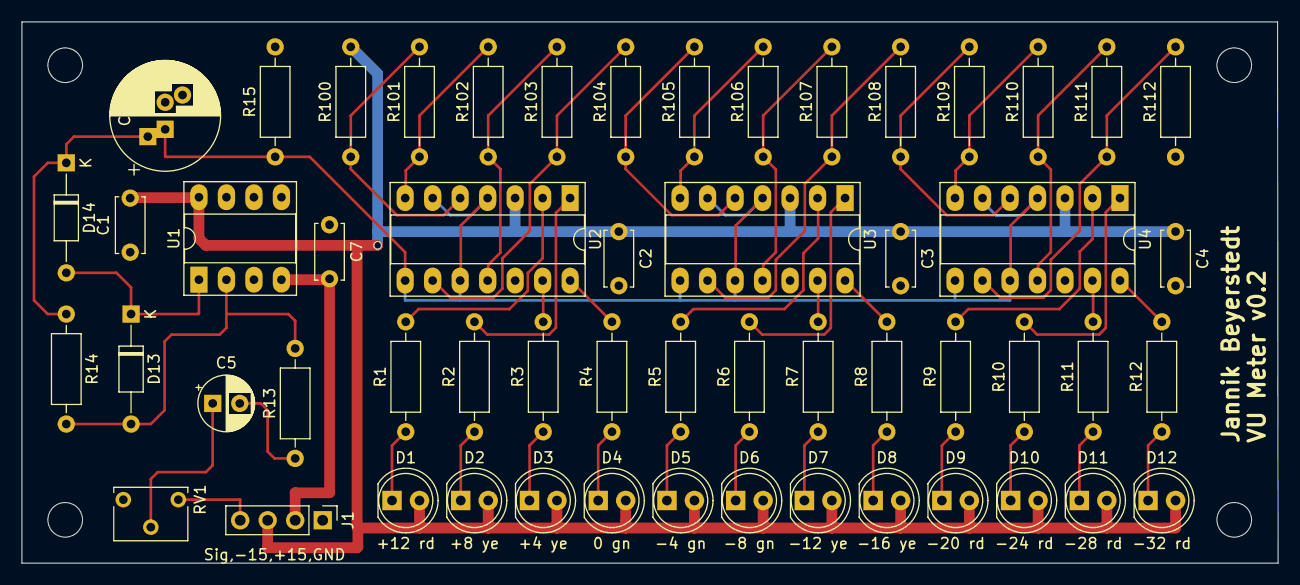
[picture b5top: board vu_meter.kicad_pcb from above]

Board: 2 copper layers, 116.1 x 50.0 mm, 59 parts (0 on the bottom side), 45 nets.
